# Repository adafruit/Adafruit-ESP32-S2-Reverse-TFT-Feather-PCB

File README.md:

## Adafruit ESP32-S2 Reverse TFT Feather PCB

<a href="http://www.adafruit.com/products/5345"><br/>
Click here to purchase one from the Adafruit shop</a>

PCB files for the Adafruit ESP32-S2 Reverse TFT Feather. 

Format is EagleCAD schematic and board layout
* https://www.adafruit.com/product/5345

### Description

Like Missy Elliot, we like to "put our [Feather] down, flip it and reverse it" and that's exactly what we've done with this new development board. It's basically our ESP32-S2 TFT Feather but with the 240x135 color TFT display on the back-side not the front-side. That makes it great for panel-mounted projects, particularly since we've also got some space for 3 buttons to go along. It's like an all-in-one display interface dev board, powered by the fantastic ESP32-S2 WIFI module.

This feather comes with native USB and 4 MB flash + 2 MB of PSRAM, so it is perfect for use with CircuitPython or Arduino with low-cost WiFi. Native USB means it can act like a keyboard or a disk drive. WiFi means it's awesome for IoT projects. And Feather means it works with the large community of Feather Wings for expandability.

The ESP32-S2 is a highly-integrated, low-power, 2.4 GHz Wi-Fi System-on-Chip (SoC) solution that now has built-in native USB as well as some other interesting new technologies like Time of Flight distance measurements. With its state-of-the-art power and RF performance, this SoC is an ideal choice for a wide variety of application scenarios relating to the Internet of Things (IoT), wearable electronics, and smart homes.

### License

Adafruit invests time and resources providing this open source design, please support Adafruit and open-source hardware by purchasing products from [Adafruit](https://www.adafruit.com)!

Designed by Limor Fried/Ladyada for Adafruit Industries.

Creative Commons Attribution/Share-Alike, all text above must be included in any redistribution. 
See license.txt for additional details.

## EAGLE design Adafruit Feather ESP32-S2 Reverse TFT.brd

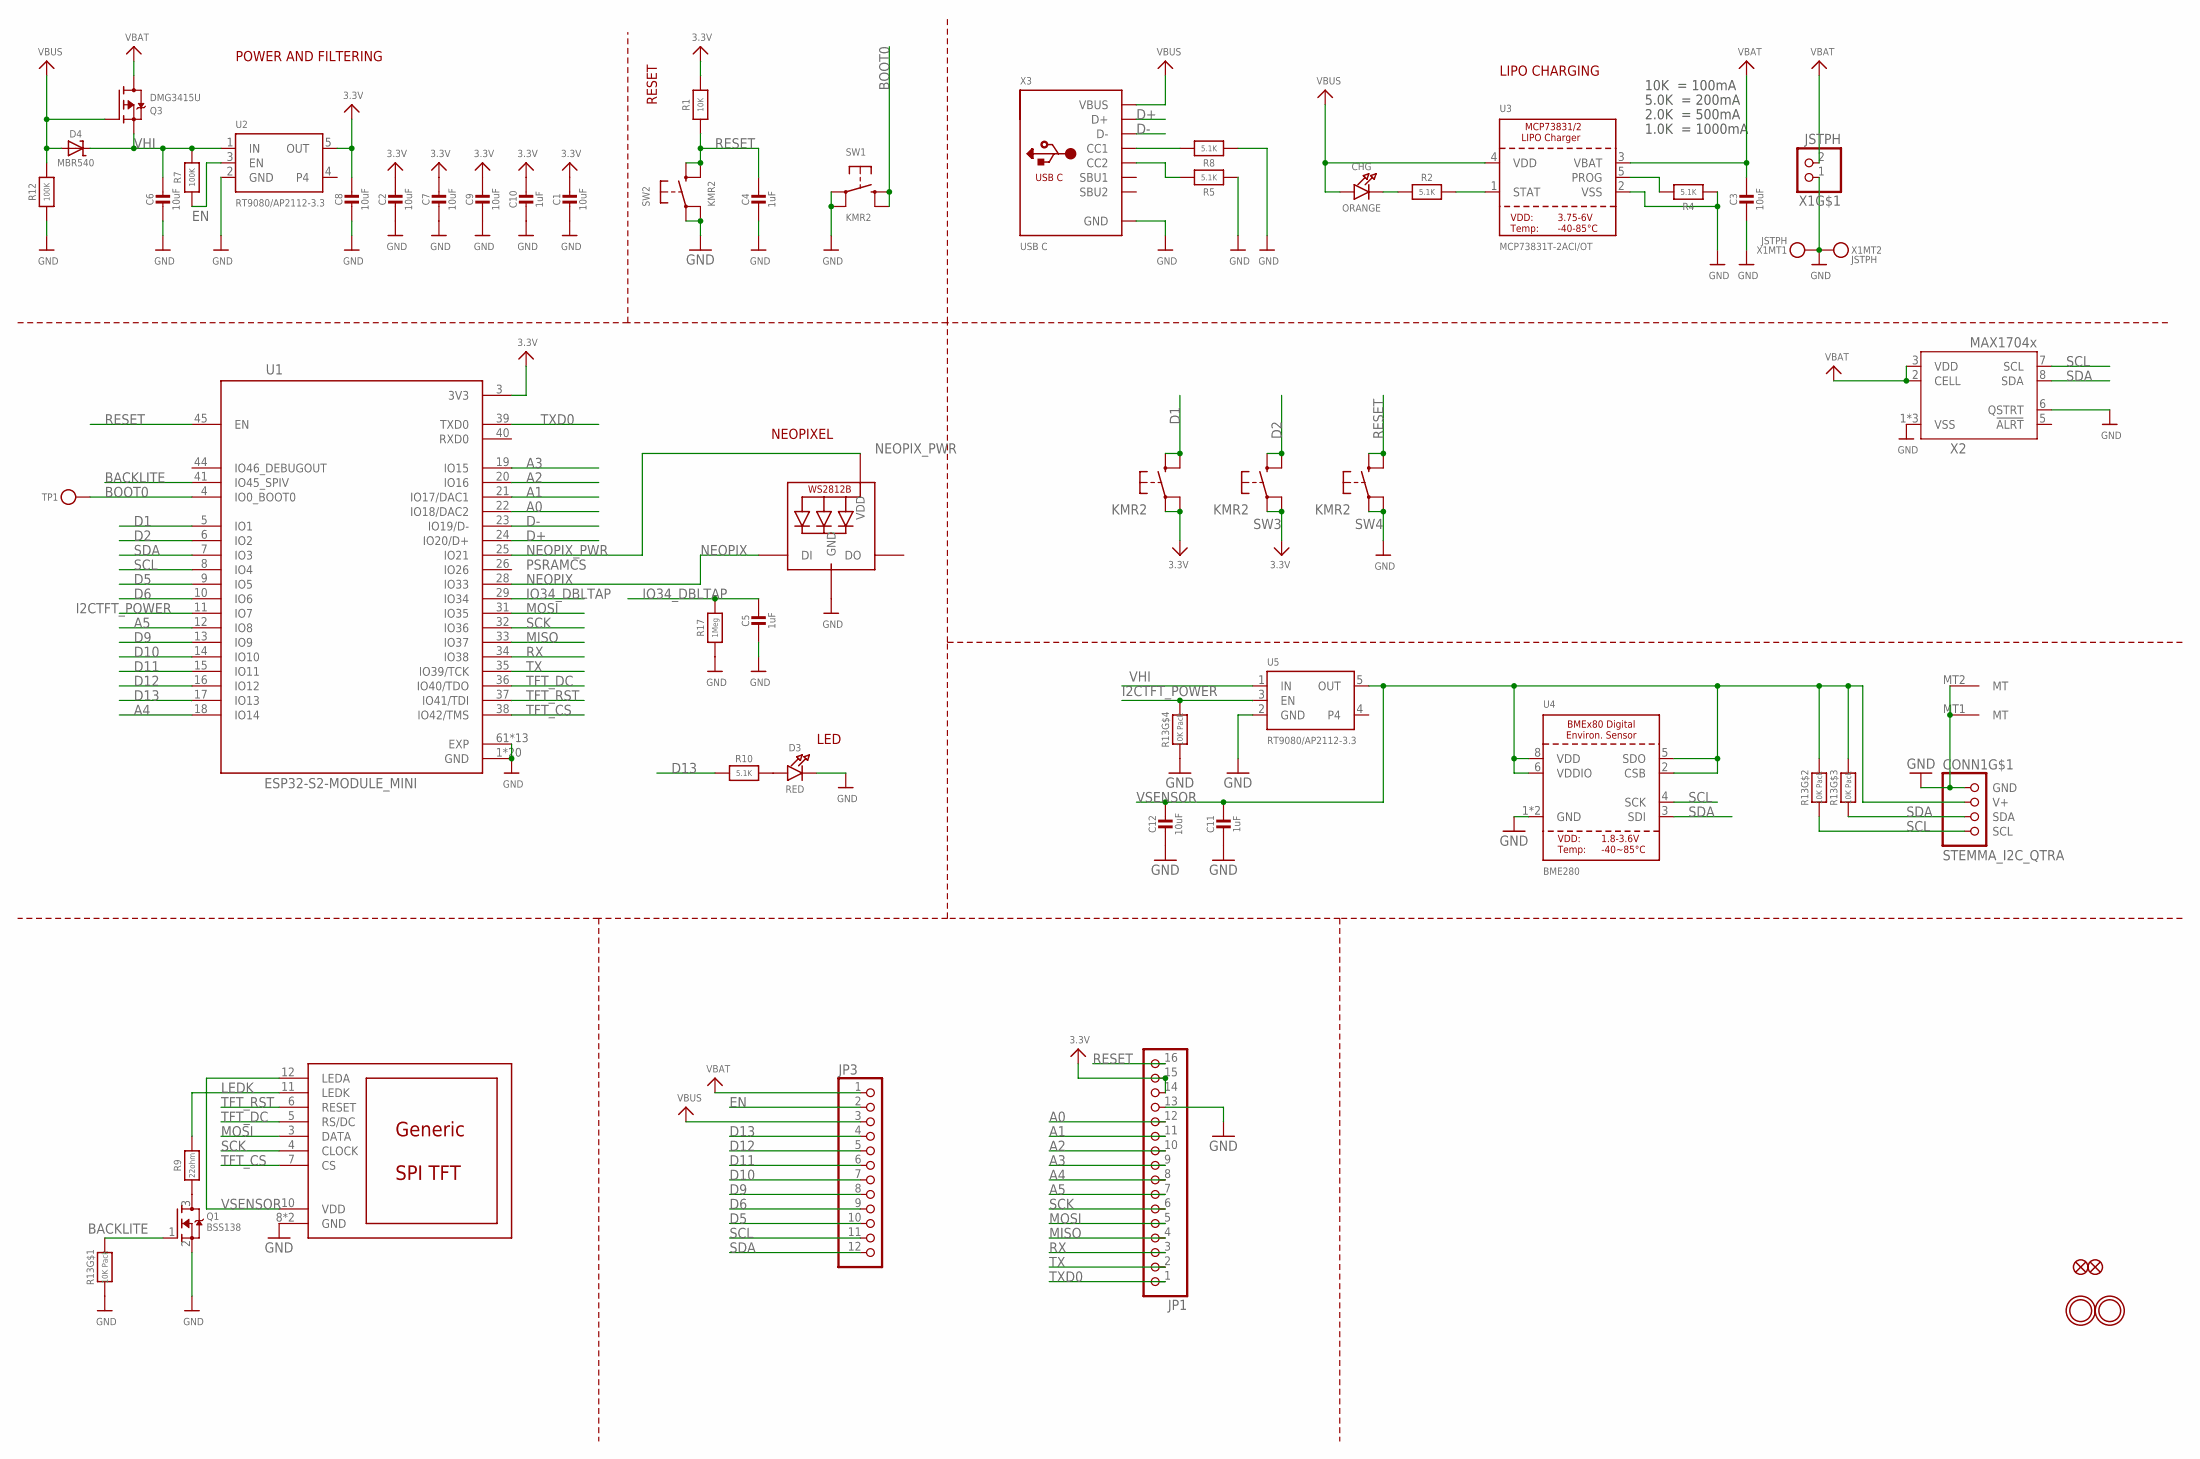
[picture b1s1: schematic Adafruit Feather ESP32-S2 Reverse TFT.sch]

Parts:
C1, C2, C3, C6, C7, C8, C9, C12: 10uF; 0805-NO
C4, C5, C10, C11: 1uF; 0603-NO
CHG: ORANGE; CHIPLED_0603_NOOUTLINE
CONN1: STEMMA_I2C_QTRA; JST_SH4_RA
D3: RED; CHIPLED_0603_NOOUTLINE
D4: MBR540; SOD-123
DISP1: DISP_LCD_GENERIC_SPI_1.14IN_240X135_WRAPUNDER; TFT_1.14IN_240X135_WRAPUNDER
JP1: HEADER-1X16_MIN; 1X16_ROUND_MIN
JP3: HEADER-1X12_MIN; 1X12_ROUND_MIN
LED1: WS2812B_SK6805_1515; SK6805_1515
Q1: BSS138; SC70
Q3: DMG3415U; SOT23-R
R1: 10K; 0603-NO
R2, R4, R5, R8, R10: 5.1K; 0603-NO
R7, R12: 100K; 0603-NO
R9: 22ohm; 0603-NO
R13: 10K Pack; RESPACK_4X0603
R17: 1Meg; 0603-NO
SW1, SW2, SW3, SW4, SW5: KMR2; BTN_RKB2_4.6X2.8
TP1: TESTPOINTROUND1.5MMNO; TESTPOINT_ROUND_1.5MM_NO
U1: ESP32-S2-MODULE_MINI; ESP32-S2-MINI-1
U2, U5: RT9080/AP2112-3.3; SOT23-5; JLC_ROTATION 0
U3: MCP73831T-2ACI/OT; SOT23-5
U4: BME280
U$31, U$32: MOUNTINGHOLE2.5; MOUNTINGHOLE_2.5_PLATED
U$34, U$35: FIDUCIAL_1MM
X1: JSTPH; JSTPH2_BATT
X2: MAX17048/T; TDFN8_2X2MM
X3: USB C; USB_C_CUSB31-CFM2AX-01-X

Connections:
3.3V: C1.1, C2.1, C7.1, C8.1, C9.1, C10.1, JP1.14, JP1.15, R1.2, SW3.A, SW3.A' (P1), SW5.A, SW5.A' (P1), U1.3 (3V3), U2.5 (OUT)
A0: JP1.12, U1.22 (IO18/DAC2)
A1: JP1.11, U1.21 (IO17/DAC1)
A2: JP1.10, U1.20 (IO16)
A3: JP1.9, U1.19 (IO15)
A4: JP1.8, U1.18 (IO14)
A5: JP1.7, U1.12 (IO8)
BACKLITE: Q1.1 (G), R13.8 (2), U1.41 (IO45_SPIV)
BOOT0: SW1.B (S), SW1.B' (S1), TP1.P$1, U1.4 (IO0_BOOT0)
D1: SW5.B (S), SW5.B' (S1), U1.5 (IO1)
D2: SW3.B (S), SW3.B' (S1), U1.6 (IO2)
D5: JP3.10, U1.9 (IO5)
D6: JP3.9, U1.10 (IO6)
D9: JP3.8, U1.13 (IO9)
D10: JP3.7, U1.14 (IO10)
D11: JP3.6, U1.15 (IO11)
D12: JP3.5, U1.16 (IO12)
D13: JP3.4, R10.1, U1.17 (IO13)
D+: U1.24 (IO20/D+), X3.A6 (D+), X3.B6 (D+)
D-: U1.23 (IO19/D-), X3.A7 (D-), X3.B7 (D-)
EN: JP3.2, R7.1, U2.3 (EN)
GND: C1.2, C2.2, C3.2, C4.2, C5.2, C6.2, C7.2, C8.2, C9.2, C10.2, C11.2, C12.2, CONN1.1 (GND), CONN1.MT1 (MT), CONN1.MT2 (MT), D3.C, DISP1.8 (GND), DISP1.13 (GND), JP1.13, LED1.4 (GND), Q1.2 (S), R4.1, R5.1, R8.1, R12.1, R13.1, R13.4 (1), R17.1, SW1.A, SW1.A' (P1), SW2.A, SW2.A' (P1), SW4.A, SW4.A' (P1), U1.1 (GND), U1.2 (GND), U1.30 (GND), U1.42 (GND), U1.43 (GND), U1.46 (GND), U1.47 (GND), U1.48 (GND), U1.49 (GND), U1.50 (GND), U1.51 (GND), U1.52 (GND), U1.53 (GND), U1.54 (GND), U1.55 (GND), U1.56 (GND), U1.57 (GND), U1.58 (GND), U1.59 (GND), U1.60 (GND), U1.61 (EXP), U1.62 (EXP), U1.63 (EXP), U1.64 (EXP), U1.65 (EXP), U1.66 (EXP), U1.67 (EXP), U1.68 (EXP), U1.69 (EXP), U1.70 (EXP), U1.71 (EXP), U1.72 (EXP), U1.73 (EXP), U2.2 (GND), U3.2 (VSS), U4.1 (GND), U4.7 (GND), U5.2 (GND), X1.1, X1.NC1, X1.NC2, X2.1 (VSS), X2.4 (VSS), X2.6 (QSTRT), X2.THERMAL (VSS), X3.A1B12 (GND), X3.B1A12 (GND)
I2CTFT_POWER: R13.5 (2), U1.11 (IO7), U5.3 (EN)
IO34_DBLTAP: C5.1, R17.2, U1.29 (IO34)
LEDK: DISP1.11 (LEDK), R9.2
MISO: JP1.4, U1.33 (IO37)
MOSI: DISP1.3 (DATA), JP1.5, U1.31 (IO35)
unnamed: CHG.C, R2.1
unnamed: Q1.3 (D), R9.1
unnamed: R2.2, U3.1 (STAT)
unnamed: R4.2, U3.5 (PROG)
unnamed: D3.A, R10.2
unnamed: R8.2, X3.A5 (CC1)
unnamed: R5.2, X3.B5 (CC2)
NEOPIX: LED1.1 (DI), U1.28 (IO33)
NEOPIX_PWR: LED1.2 (VDD), U1.25 (IO21)
RESET: C4.1, JP1.16, R1.1, SW2.B (S), SW2.B' (S1), SW4.B (S), SW4.B' (S1), U1.45 (EN)
RX: JP1.3, U1.34 (IO38)
SCK: DISP1.4 (CLOCK), JP1.6, U1.32 (IO36)
SCL: CONN1.4 (SCL), JP3.11, R13.2 (1), U1.8 (IO4), U4.4 (SCK), X2.7 (SCL)
SDA: CONN1.3 (SDA), JP3.12, R13.3 (1), U1.7 (IO3), U4.3 (SDI), X2.8 (SDA)
TFT_CS: DISP1.7 (CS), U1.38 (IO42/TMS)
TFT_DC: DISP1.5 (RS/DC), U1.36 (IO40/TDO)
TFT_RST: DISP1.6 (RESET), U1.37 (IO41/TDI)
TX: JP1.2, U1.35 (IO39/TCK)
TXD0: JP1.1, U1.39 (TXD0)
VBAT: C3.1, JP3.1, Q3.3 (D), U3.3 (VBAT), X1.2, X2.2 (CELL), X2.3 (VDD)
VBUS: CHG.A, D4.A, JP3.3, Q3.1 (G), R12.2, U3.4 (VDD), X3.A4B9 (VBUS), X3.B4A9 (VBUS)
VHI: C6.1, D4.C, Q3.2 (S), R7.2, U2.1 (IN), U5.1 (IN)
VSENSOR: C11.1, C12.1, CONN1.2 (V+), DISP1.10 (VDD), DISP1.12 (LEDA), R13.6 (2), R13.7 (2), U4.2 (CSB), U4.5 (SDO), U4.6 (VDDIO), U4.8 (VDD), U5.5 (OUT)

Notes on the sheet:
POWER AND FILTERING
RESET
10K = 100mA
5.0K = 200mA
2.0K = 500mA
1.0K = 1000mA
LIPO CHARGING
LED
PSRAMCS
NEOPIXEL

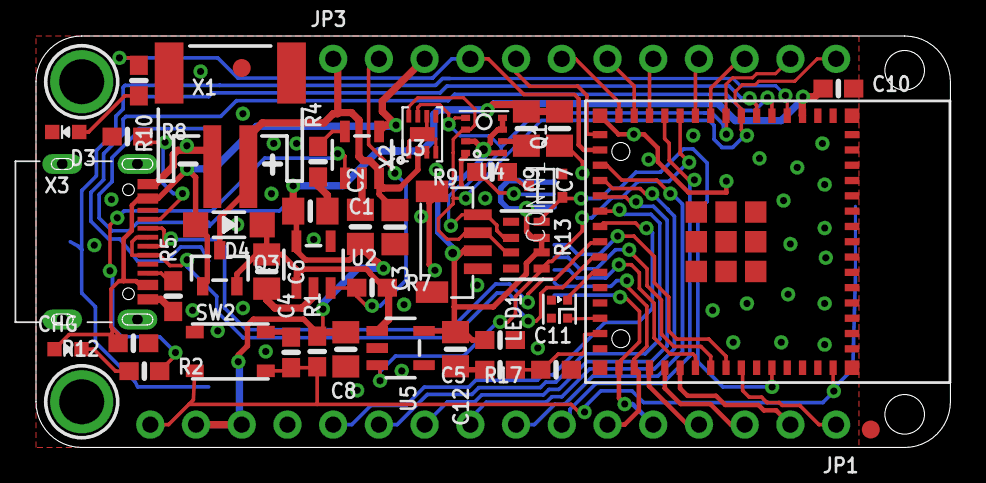
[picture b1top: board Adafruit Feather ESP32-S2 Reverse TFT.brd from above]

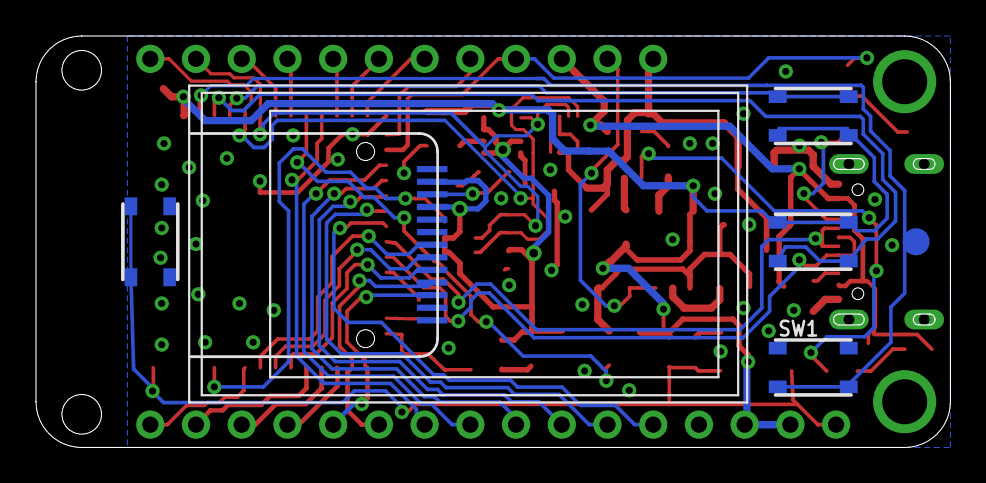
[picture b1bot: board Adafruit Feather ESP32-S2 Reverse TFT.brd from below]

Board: 2 copper layers, 50.8 x 22.9 mm, 88 parts (11 on the bottom side), 50 nets.

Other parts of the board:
PLABEL0: PLABEL0
PLABEL1: PLABEL1
PLABEL2: PLABEL2
PLABEL3: PLABEL3
PLABEL4: PLABEL4
PLABEL5: PLABEL5
PLABEL6: PLABEL6
PLABEL7: PLABEL7
PLABEL8: PLABEL8
PLABEL9: PLABEL9
PLABEL10: PLABEL10
PLABEL11: PLABEL11
PLABEL12: PLABEL12
PLABEL13: PLABEL13
PLABEL14: PLABEL14
PLABEL15: PLABEL15
PLABEL16: PLABEL16
PLABEL17: PLABEL17
PLABEL18: PLABEL18
PLABEL19: PLABEL19
PLABEL20: PLABEL20
PLABEL21: PLABEL21
PLABEL22: PLABEL22
PLABEL23: PLABEL23
PLABEL24: PLABEL24
PLABEL25: PLABEL25
PLABEL26: PLABEL26
PLABEL27: PLABEL27
PLABEL28: PLABEL28
PLABEL29: PLABEL29
PLABEL30: PLABEL30
PLABEL31: PLABEL31
PLABEL32: PLABEL32
PLABEL33: PLABEL33
PLABEL34: PLABEL34
PLABEL35: PLABEL35
PLABEL36: PLABEL36

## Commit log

2023-02-06 Added board files
2023-02-07 Add factory reset file
2023-02-07 Add PrettyPins PDFs.
2023-02-17 Add PrettyPins
2023-02-17 Add PrettyPins PDF
2023-08-09 Incorrect pins. Deleting for replacement.
2023-08-09 Now with correct pin information!

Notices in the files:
parts and their libraries:
microbuilder: This work is placed in the public domain, and may be freely used for commercial and non-commercial work with the following conditions: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
